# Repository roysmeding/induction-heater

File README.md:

# Induction heater design files

## Disclaimer
WARNING: THIS DESIGN IS UNTESTED. ADDITIONALLY, IF YOU ATTEMPT TO BUILD ONE
OF THESE WITHOUT FULLY UNDERSTANDING WHAT YOU'RE DOING, YOU WILL PROBABLY DIE.
DON'T SAY I DIDN'T WARN YOU!

## Introduction
Now that that's out of the way: this repository contains the design files for
an induction heater meant to heat metals to forging or melting temperature.

Rough specs:

- 3.5kW design power (just right for a standard 230V circuit in the Netherlands)
- Water-cooled work coil so we can heat fairly conductive metal like aluminium
- Main power stage uses salvaged parts from an induction cooktop.
- Microcontroller-based control system

This project is still very much a work in progress, but some preliminary design
files are available, as well as simulation work.

## License
This work is licensed under the Creative Commons Attribution 4.0 International
License. To view a copy of this license, visit http://creativecommons.org/licenses/by/4.0/.

## Contact
Your best bet is to contact the primary suspect (Roy Smeding; roy.smeding@gmail.com)
for more information.

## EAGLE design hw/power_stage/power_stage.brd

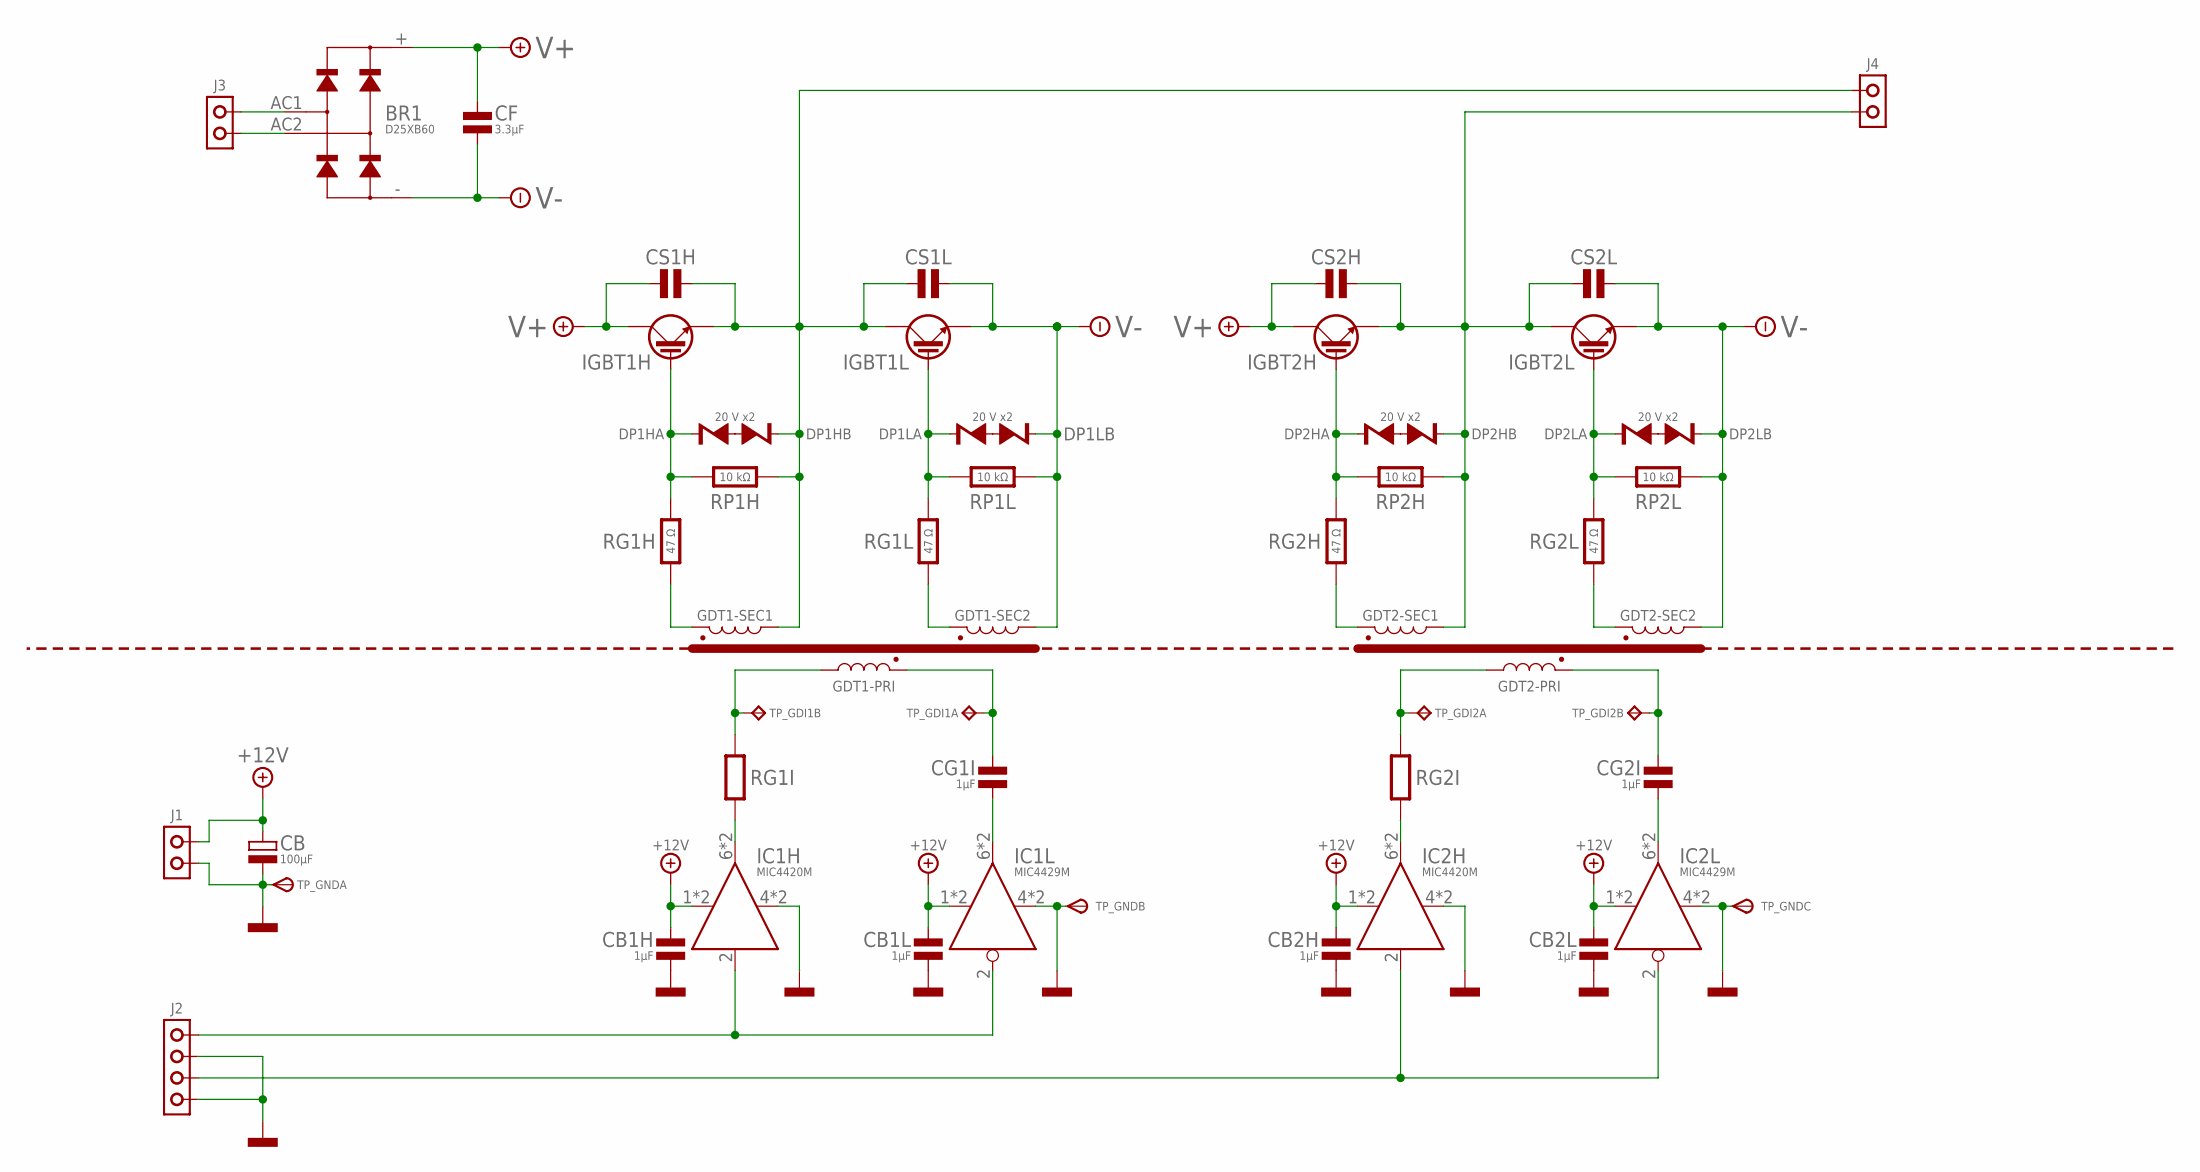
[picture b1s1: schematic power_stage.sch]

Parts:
BR1: D25XB60
CB: 100µF; CPOL-PANASONIC-B
CB1H, CB1L, CB2H, CB2L: 1µF; C-0805
CF: 3.3µF; C-R75
CG1I, CG2I: 1µF; C-0805
CS1H, CS1L, CS2H, CS2L: C_R76; C-R76
DP1HA, DP1HB, DP1LA, DP1LB, DP2HA, DP2HB, DP2LA, DP2LB: 20 V; SOD80C
GDT1, GDT2: GDT
IC1H, IC2H: MIC4420M; SO-08
IC1L, IC2L: MIC4429M; SO-08
IGBT1H, IGBT1L, IGBT2H, IGBT2L: IXGR32N60CD1; TO-247AD-V
J1: CON-2POS-NS25
J2: CON-4POS-NS25
J3, J4: CON-2POS-MNL; TE-350824-1
RG1H, RG1L, RG2H, RG2L: 47 Ω; R-0805
RG1I, RG2I: R-0805
RP1H, RP1L, RP2H, RP2L: 10 kΩ; R-0805
TP_GDI1A, TP_GDI2B: A; TP10SQ
TP_GDI1B, TP_GDI2A: B; TP10SQ
TP_GNDA: GND; P1-13
TP_GNDB: GND; P1-13
TP_GNDC: GND; P1-13

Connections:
+12V: CB.+, CB1H.1, CB1L.1, CB2H.1, CB2L.1, IC1H.1 (VS), IC1H.8 (VS), IC1L.1 (VS), IC1L.8 (VS), IC2H.1 (VS), IC2H.8 (VS), IC2L.1 (VS), IC2L.8 (VS), J1.1
AC1: BR1.AC1, J3.1
AC2: BR1.AC2, J3.2
GND: CB.-, CB1H.2, CB1L.2, CB2H.2, CB2L.2, IC1H.4 (GND), IC1H.5 (GND), IC1L.4 (GND), IC1L.5 (GND), IC2H.4 (GND), IC2H.5 (GND), IC2L.4 (GND), IC2L.5 (GND), J1.2, J2.2, J2.4, TP_GNDA.TP, TP_GNDB.TP, TP_GNDC.TP
unnamed: GDT1.PRI-2 (2), RG1I.2, TP_GDI1B.TP
unnamed: IC1H.6 (OUT), IC1H.7 (OUT), RG1I.1
unnamed: GDT1.SEC1-1 (1), RG1H.1
unnamed: IC2H.6 (OUT), IC2H.7 (OUT), RG2I.1
unnamed: GDT2.PRI-2 (2), RG2I.2, TP_GDI2A.TP
unnamed: DP1LA.C, IGBT1L.G, RG1L.2, RP1L.2
unnamed: GDT1.SEC2-1 (1), RG1L.1
unnamed: DP2LA.C, IGBT2L.G, RG2L.2, RP2L.2
unnamed: DP1HA.C, IGBT1H.G, RG1H.2, RP1H.2
unnamed: GDT2.SEC2-1 (1), RG2L.1
unnamed: GDT2.SEC1-1 (1), RG2H.1
unnamed: DP2HA.C, IGBT2H.G, RG2H.2, RP2H.2
unnamed: IC1H.2 (IN), IC1L.2 (IN), J2.1
unnamed: DP1LA.A, DP1LB.A
unnamed: DP1HA.A, DP1HB.A
unnamed: IC2H.2 (IN), IC2L.2 (IN), J2.3
unnamed: CG1I.2, IC1L.6 (OUT), IC1L.7 (OUT)
unnamed: DP2HA.A, DP2HB.A
unnamed: DP2LA.A, DP2LB.A
unnamed: CG2I.2, IC2L.6 (OUT), IC2L.7 (OUT)
unnamed: CG1I.1, GDT1.PRI-1 (1), TP_GDI1A.TP
unnamed: CG2I.1, GDT2.PRI-1 (1), TP_GDI2B.TP
OUT1: CS1H.P$1, CS1L.P$2, DP1HB.C, GDT1.SEC1-2 (2), IGBT1H.S (E), IGBT1L.D (C), J4.1, RP1H.1
OUT2: CS2H.P$1, CS2L.P$2, DP2HB.C, GDT2.SEC1-2 (2), IGBT2H.S (E), IGBT2L.D (C), J4.2, RP2H.1
V+: BR1.+, CF.P$2, CS1H.P$2, CS2H.P$2, IGBT1H.D (C), IGBT2H.D (C)
V-: BR1.-, CF.P$1, CS1L.P$1, CS2L.P$1, DP1LB.C, DP2LB.C, GDT1.SEC2-2 (2), GDT2.SEC2-2 (2), IGBT1L.S (E), IGBT2L.S (E), RP1L.1, RP2L.1

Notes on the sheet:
20 V x2

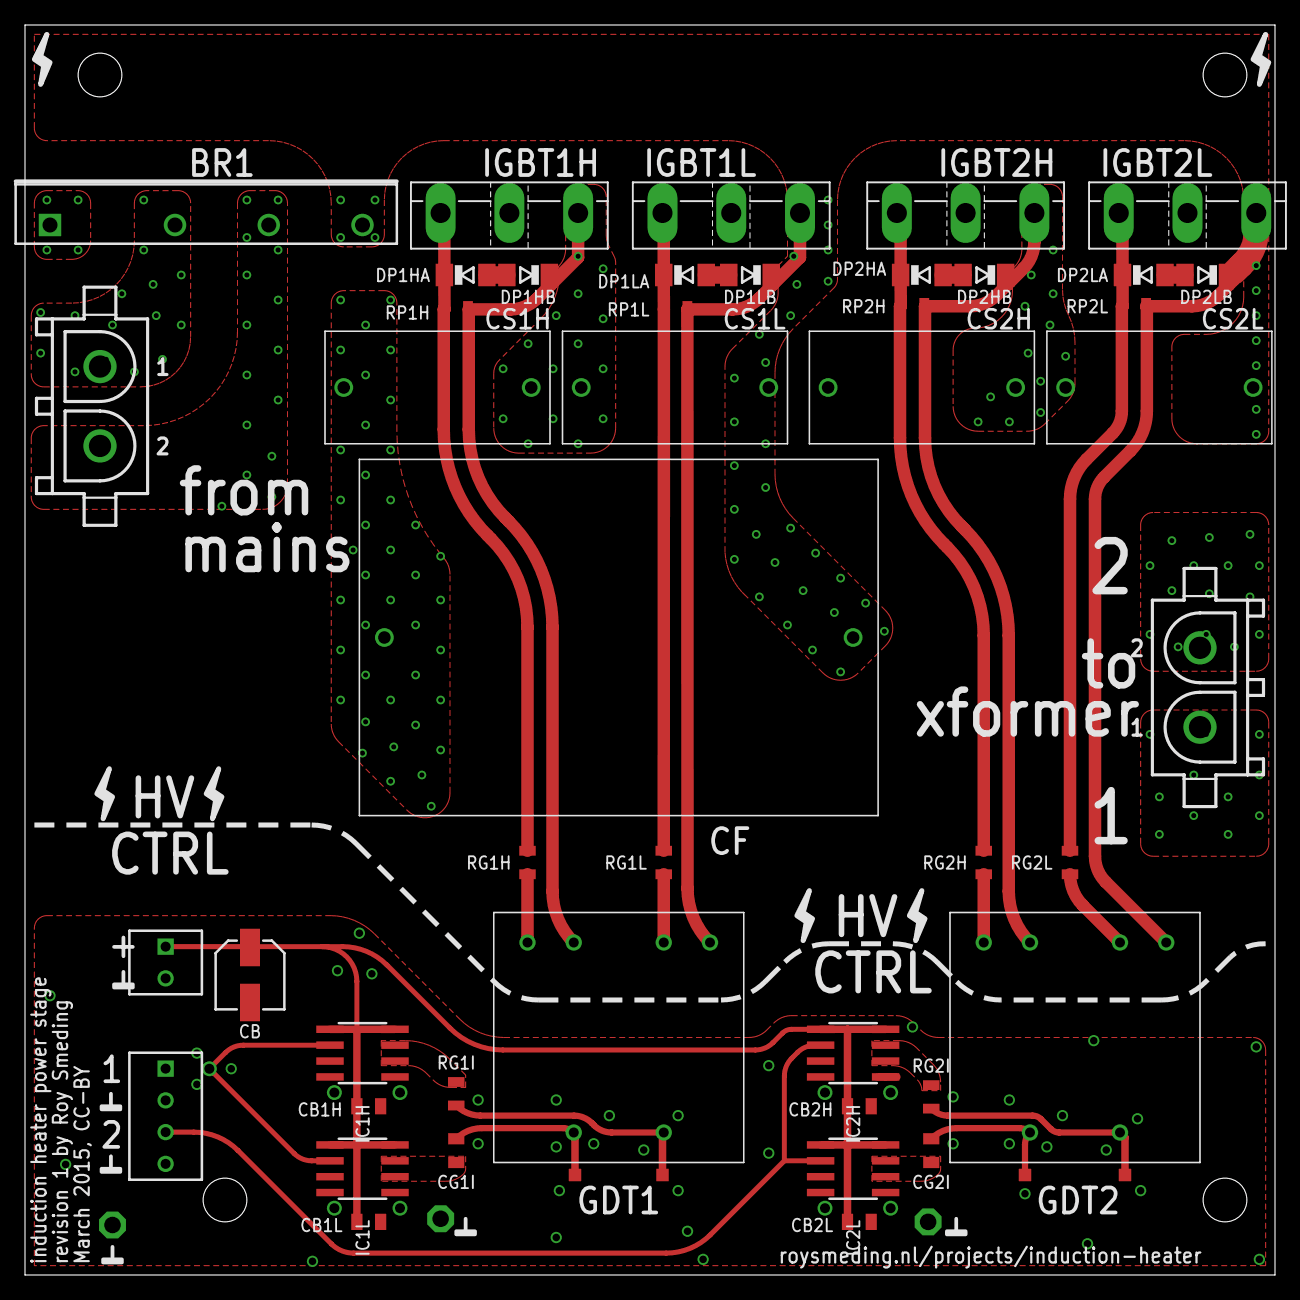
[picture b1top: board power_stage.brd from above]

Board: 2 copper layers, 100.0 x 100.0 mm, 52 parts (0 on the bottom side), 30 nets.

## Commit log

2015-03-06 Initial commit; basic untested design is here
2015-03-09 Updated README, wiggle about some stuff
2015-03-09 Adapted power_stage.brd to be 100x100mm
    This enables us to use cheap PCB fab services.
2015-03-09 Removed some simulations that seem woefully incorrect.
2015-03-09 More cleanup
2015-03-12 Remove solder mask from high current tracks so we can cheaply increase their current capacity
2015-03-13 More fiddling
2015-03-16 Add URL to board
2015-03-16 Fix unconnected output pin on gate driver ICs
2015-03-19 why not
2015-03-19 Move some vias
2015-03-20 REVISION ONE!
2015-07-06 Fix README.md typo
2015-08-18 Power stage: fix incorrect GDT footprint
    Turns out I must've measured wrong when i determined the polarity of the
    GDT windings, but one of the secondary windings has the opposite
    polarity to what I had in the layout. Makes sense, since this does make
    the layout somewhat more direct.
    Doesn't matter much now since my boards have already been produced (I'll
    be patching them by hand) and it's unlikely anyone will end up using the
2016-09-18 Added STM32F334 (microcontroller) to library, newer EAGLE project version
2016-09-18 Uninteresting changes from desktop
2016-09-18 Clean up the power stage schematic
    This means the board changed a bit too
2016-09-19 Changed power stage PCB connectors

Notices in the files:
hw/power_stage/power_stage.brd:
March 2015, CC-BY
